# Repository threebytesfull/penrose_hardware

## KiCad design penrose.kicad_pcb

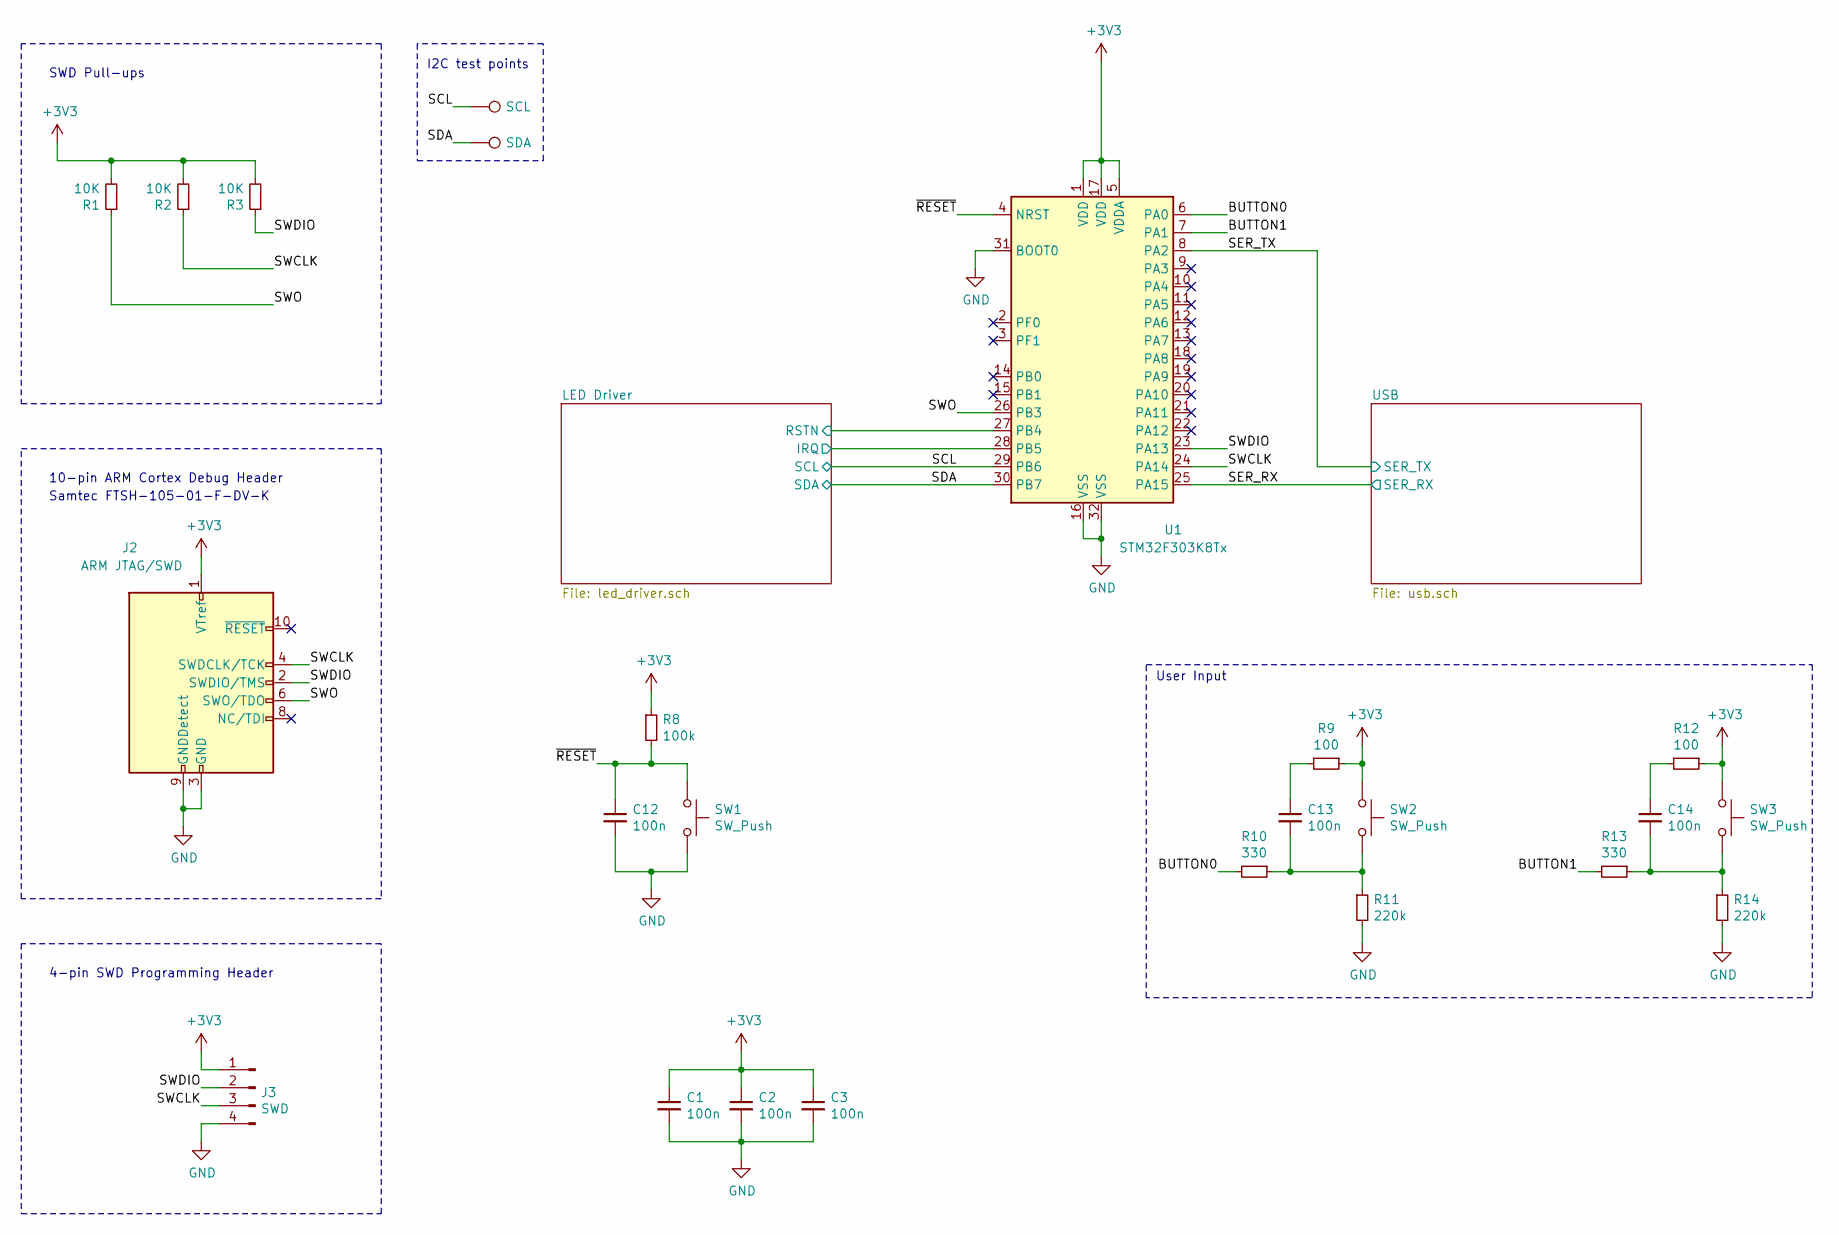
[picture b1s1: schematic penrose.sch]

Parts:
C1, C2, C3, C12, C13, C14: 100n; C_0603_1608Metric
J2: ARM JTAG/SWD; FTSH-105-01-F-DV-K_HandSolder
J3: SWD; Harwin_M20-88900445_1x04_P2.54mm_Horizontal
R1, R2, R3: 10K; R_0603_1608Metric
R8: 100k; R_0603_1608Metric
R9, R12: 100; R_0603_1608Metric
R10, R13: 330; R_0603_1608Metric
R11, R14: 220k; R_0603_1608Metric
SW1, SW2, SW3: SW_Push; SW_SPST_B3U-1000P_HandSolder
TP12: SCL; TestPoint_Pad_D1.0mm
TP13: SDA; TestPoint_Pad_D1.0mm
U1: STM32F303K8Tx; LQFP-32_7x7mm_P0.8mm_Clear

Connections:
+3V3: C1.1, C2.1, C3.1, J2.1 (VTref), J3.1, R1.2, R2.2, R3.2, R8.1, R9.1, R12.1, SW2.1, SW3.1, U1.1 (VDD), U1.5 (VDDA), U1.17 (VDD); also elsewhere on the board
/BUTTON0: R10.2, U1.6 (PA0)
/BUTTON1: R13.2, U1.7 (PA1)
/LED Driver/IRQ: U1.28 (PB5); also elsewhere on the board
/LED Driver/RSTN: U1.27 (PB4); also elsewhere on the board
/SCL: TP12.1, U1.29 (PB6); also elsewhere on the board
/SDA: TP13.1, U1.30 (PB7); also elsewhere on the board
/SER_RX: U1.25 (PA15); also elsewhere on the board
/SER_TX: U1.8 (PA2); also elsewhere on the board
/SWCLK: J2.4 (SWDCLK/TCK), J3.3, R2.1, U1.24 (PA14)
/SWDIO: J2.2 (SWDIO/TMS), J3.2, R3.1, U1.23 (PA13)
/SWO: J2.6 (SWO/TDO), R1.1, U1.26 (PB3)
/~RESET: C12.1, R8.2, SW1.1, U1.4 (NRST)
GND: C1.2, C2.2, C3.2, C12.2, J2.3 (GND), J2.5 (GND), J2.9 (GNDDetect), J3.4, R11.2, R14.2, SW1.2, U1.16 (VSS), U1.31 (BOOT0), U1.32 (VSS); also elsewhere on the board
unnamed: C13.1, R9.2
unnamed: C13.2, R10.1, R11.1, SW2.2
unnamed: C14.1, R12.2
unnamed: C14.2, R13.1, R14.1, SW3.2

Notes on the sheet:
4-pin SWD Programming Header
10-pin ARM Cortex Debug Header
SWD Pull-ups
Samtec FTSH-105-01-F-DV-K
I2C test points
User Input

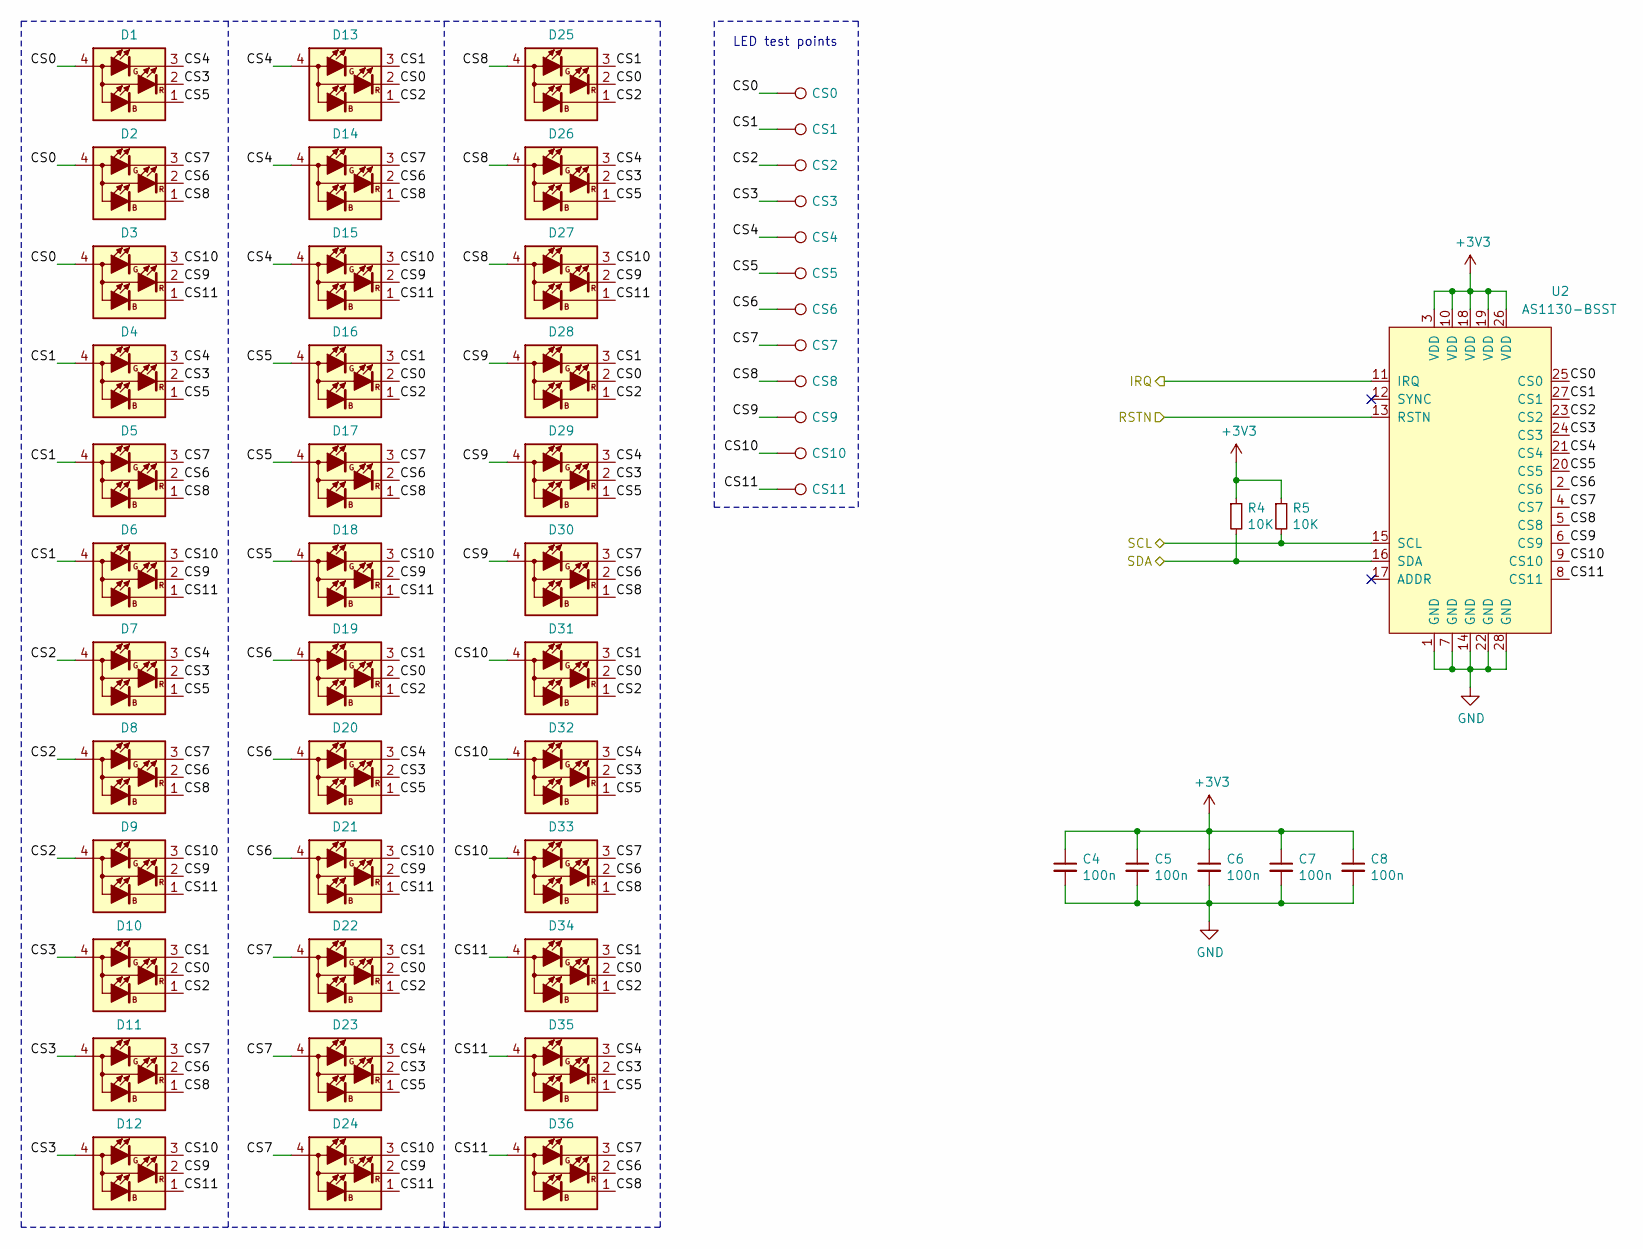
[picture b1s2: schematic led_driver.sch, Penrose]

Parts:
C4, C5, C6, C7, C8: 100n; C_0603_1608Metric
D1, D2, D3, D4, D5, D6, D7, D8, D9, D10, D11, D12, D13, D14, D15, D16, D17, D18, D19, D20, D21, D22, D23, D24, D25, D26, D27, D28, D29, D30, D31, D32, D33, D34, D35, D36: ARGB1313HS-TR_CommonAnode; LED_0808_Metric2020_CommonAnode
R4, R5: 10K; R_0603_1608Metric
TP0: CS0; TestPoint_Pad_D1.0mm
TP1: CS1; TestPoint_Pad_D1.0mm
TP2: CS2; TestPoint_Pad_D1.0mm
TP3: CS3; TestPoint_Pad_D1.0mm
TP4: CS4; TestPoint_Pad_D1.0mm
TP5: CS5; TestPoint_Pad_D1.0mm
TP6: CS6; TestPoint_Pad_D1.0mm
TP7: CS7; TestPoint_Pad_D1.0mm
TP8: CS8; TestPoint_Pad_D1.0mm
TP9: CS9; TestPoint_Pad_D1.0mm
TP10: CS10; TestPoint_Pad_D1.0mm
TP11: CS11; TestPoint_Pad_D1.0mm
U2: AS1130-BSST; SSOP-28_5.3x10.2mm_P0.65mm_Clear

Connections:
+3V3: C4.1, C5.1, C6.1, C7.1, C8.1, R4.1, R5.1, U2.3 (VDD), U2.10 (VDD), U2.18 (VDD), U2.19 (VDD), U2.26 (VDD); also elsewhere on the board
/LED Driver/CS0: D1.4 (A), D2.4 (A), D3.4 (A), D10.2 (KR), D13.2 (KR), D16.2 (KR), D19.2 (KR), D22.2 (KR), D25.2 (KR), D28.2 (KR), D31.2 (KR), D34.2 (KR), TP0.1, U2.25 (CS0)
/LED Driver/CS1: D4.4 (A), D5.4 (A), D6.4 (A), D10.3 (KG), D13.3 (KG), D16.3 (KG), D19.3 (KG), D22.3 (KG), D25.3 (KG), D28.3 (KG), D31.3 (KG), D34.3 (KG), TP1.1, U2.27 (CS1)
/LED Driver/CS2: D7.4 (A), D8.4 (A), D9.4 (A), D10.1 (KB), D13.1 (KB), D16.1 (KB), D19.1 (KB), D22.1 (KB), D25.1 (KB), D28.1 (KB), D31.1 (KB), D34.1 (KB), TP2.1, U2.23 (CS2)
/LED Driver/CS3: D1.2 (KR), D4.2 (KR), D7.2 (KR), D10.4 (A), D11.4 (A), D12.4 (A), D20.2 (KR), D23.2 (KR), D26.2 (KR), D29.2 (KR), D32.2 (KR), D35.2 (KR), TP3.1, U2.24 (CS3)
/LED Driver/CS4: D1.3 (KG), D4.3 (KG), D7.3 (KG), D13.4 (A), D14.4 (A), D15.4 (A), D20.3 (KG), D23.3 (KG), D26.3 (KG), D29.3 (KG), D32.3 (KG), D35.3 (KG), TP4.1, U2.21 (CS4)
/LED Driver/CS5: D1.1 (KB), D4.1 (KB), D7.1 (KB), D16.4 (A), D17.4 (A), D18.4 (A), D20.1 (KB), D23.1 (KB), D26.1 (KB), D29.1 (KB), D32.1 (KB), D35.1 (KB), TP5.1, U2.20 (CS5)
/LED Driver/CS6: D2.2 (KR), D5.2 (KR), D8.2 (KR), D11.2 (KR), D14.2 (KR), D17.2 (KR), D19.4 (A), D20.4 (A), D21.4 (A), D30.2 (KR), D33.2 (KR), D36.2 (KR), TP6.1, U2.2 (CS6)
/LED Driver/CS7: D2.3 (KG), D5.3 (KG), D8.3 (KG), D11.3 (KG), D14.3 (KG), D17.3 (KG), D22.4 (A), D23.4 (A), D24.4 (A), D30.3 (KG), D33.3 (KG), D36.3 (KG), TP7.1, U2.4 (CS7)
/LED Driver/CS8: D2.1 (KB), D5.1 (KB), D8.1 (KB), D11.1 (KB), D14.1 (KB), D17.1 (KB), D25.4 (A), D26.4 (A), D27.4 (A), D30.1 (KB), D33.1 (KB), D36.1 (KB), TP8.1, U2.5 (CS8)
/LED Driver/CS9: D3.2 (KR), D6.2 (KR), D9.2 (KR), D12.2 (KR), D15.2 (KR), D18.2 (KR), D21.2 (KR), D24.2 (KR), D27.2 (KR), D28.4 (A), D29.4 (A), D30.4 (A), TP9.1, U2.6 (CS9)
/LED Driver/CS10: D3.3 (KG), D6.3 (KG), D9.3 (KG), D12.3 (KG), D15.3 (KG), D18.3 (KG), D21.3 (KG), D24.3 (KG), D27.3 (KG), D31.4 (A), D32.4 (A), D33.4 (A), TP10.1, U2.9 (CS10)
/LED Driver/CS11: D3.1 (KB), D6.1 (KB), D9.1 (KB), D12.1 (KB), D15.1 (KB), D18.1 (KB), D21.1 (KB), D24.1 (KB), D27.1 (KB), D34.4 (A), D35.4 (A), D36.4 (A), TP11.1, U2.8 (CS11)
/LED Driver/IRQ: U2.11 (IRQ); also elsewhere on the board
/LED Driver/RSTN: U2.13 (RSTN); also elsewhere on the board
/SCL: R5.2, U2.15 (SCL); also elsewhere on the board
/SDA: R4.2, U2.16 (SDA); also elsewhere on the board
GND: C4.2, C5.2, C6.2, C7.2, C8.2, U2.1 (GND), U2.7 (GND), U2.14 (GND), U2.22 (GND), U2.28 (GND); also elsewhere on the board

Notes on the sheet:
LED test points

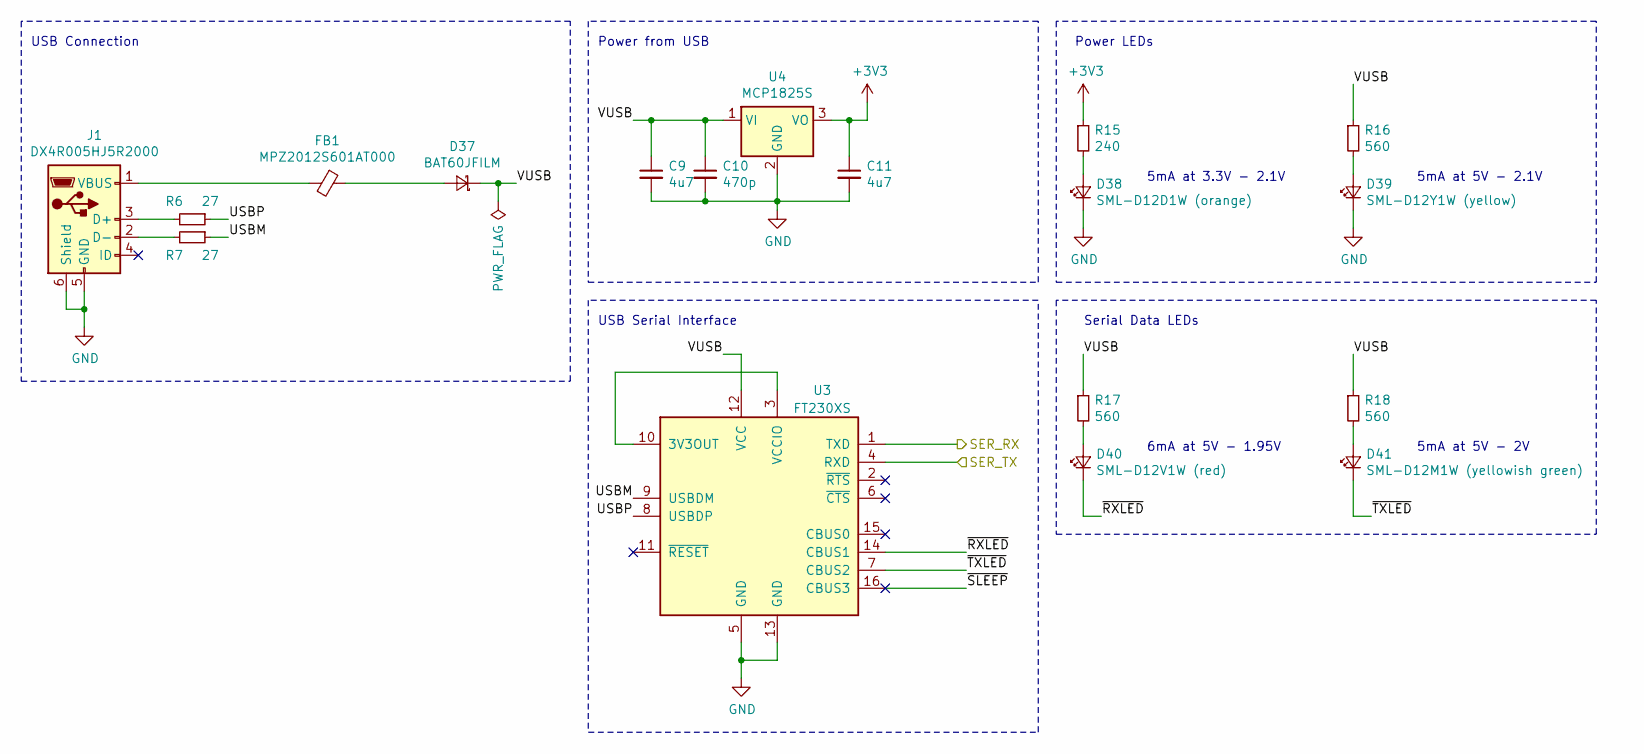
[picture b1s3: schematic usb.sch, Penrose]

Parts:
C9, C11: 4u7; C_0603_1608Metric
C10: 470p; C_0603_1608Metric
D37: BAT60JFILM; D_SOD-323_HandSoldering
D38: SML-D12D1W (orange); LED_0603_1608Metric
D39: SML-D12Y1W (yellow); LED_0603_1608Metric
D40: SML-D12V1W (red); LED_0603_1608Metric
D41: SML-D12M1W (yellowish green); LED_0603_1608Metric
FB1: MPZ2012S601AT000; L_0805_2012Metric
J1: DX4R005HJ5R2000; DX4R005HJ5_HandSolder
R6, R7: 27; R_0603_1608Metric
R15: 240; R_0603_1608Metric
R16, R17, R18: 560; R_0603_1608Metric
U3: FT230XS; SSOP-16_3.9x4.9mm_P0.635mm_Clear
U4: MCP1825S; SOT-223-3_TabPin2

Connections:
+3V3: C11.1, R15.1, U4.3 (VO); also elsewhere on the board
/SER_RX: U3.1 (TXD); also elsewhere on the board
/SER_TX: U3.4 (RXD); also elsewhere on the board
/USB/USBM: R7.1, U3.9 (USBDM)
/USB/USBP: R6.1, U3.8 (USBDP)
/USB/VUSB: C9.1, C10.1, D37.1 (K), R16.1, R17.1, R18.1, U3.12 (VCC), U4.1 (VI)
/USB/~RXLED: D40.1 (K), U3.14 (CBUS1)
/USB/~TXLED: D41.1 (K), U3.7 (CBUS2)
GND: C9.2, C10.2, C11.2, D38.1 (K), D39.1 (K), J1.5 (GND), J1.6 (Shield), U3.5 (GND), U3.13 (GND), U4.2 (GND); also elsewhere on the board
unnamed: D37.2 (A), FB1.1
unnamed: D38.2 (A), R15.2
unnamed: D39.2 (A), R16.2
unnamed: D40.2 (A), R17.2
unnamed: D41.2 (A), R18.2
unnamed: FB1.2, J1.1 (VBUS)
unnamed: J1.2 (D-), R7.2
unnamed: J1.3 (D+), R6.2
unnamed: U3.3 (VCCIO), U3.10 (3V3OUT)

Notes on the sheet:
5mA at 5V - 2.1V
5mA at 3.3V - 2.1V
5mA at 5V - 2V
6mA at 5V - 1.95V
Power LEDs
Serial Data LEDs
Power from USB
USB Serial Interface
USB Connection

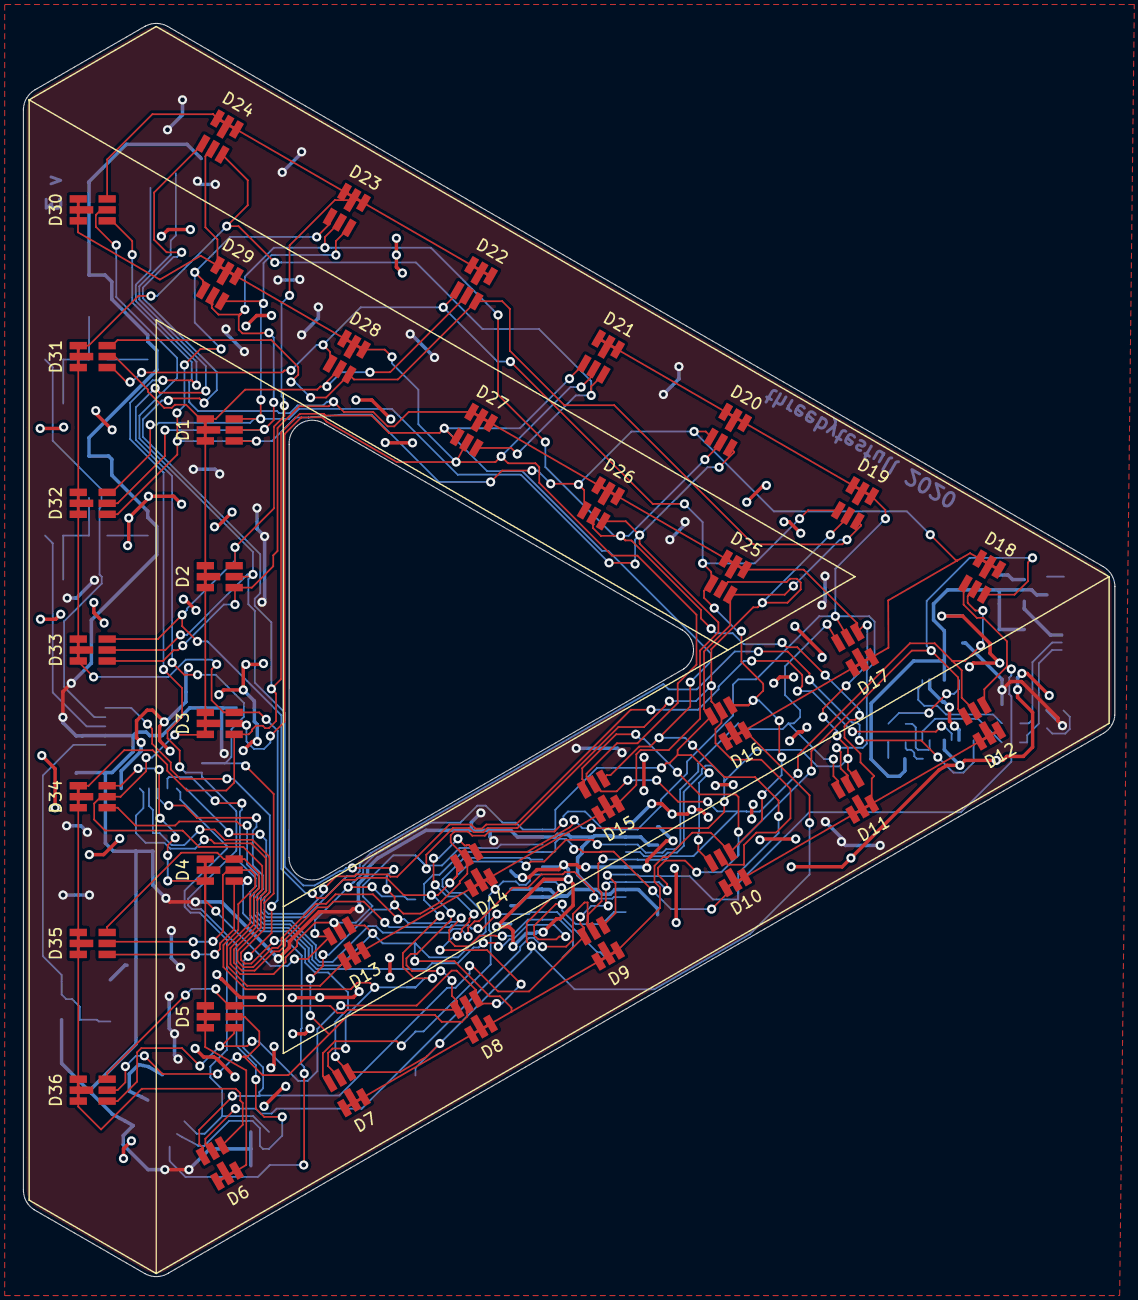
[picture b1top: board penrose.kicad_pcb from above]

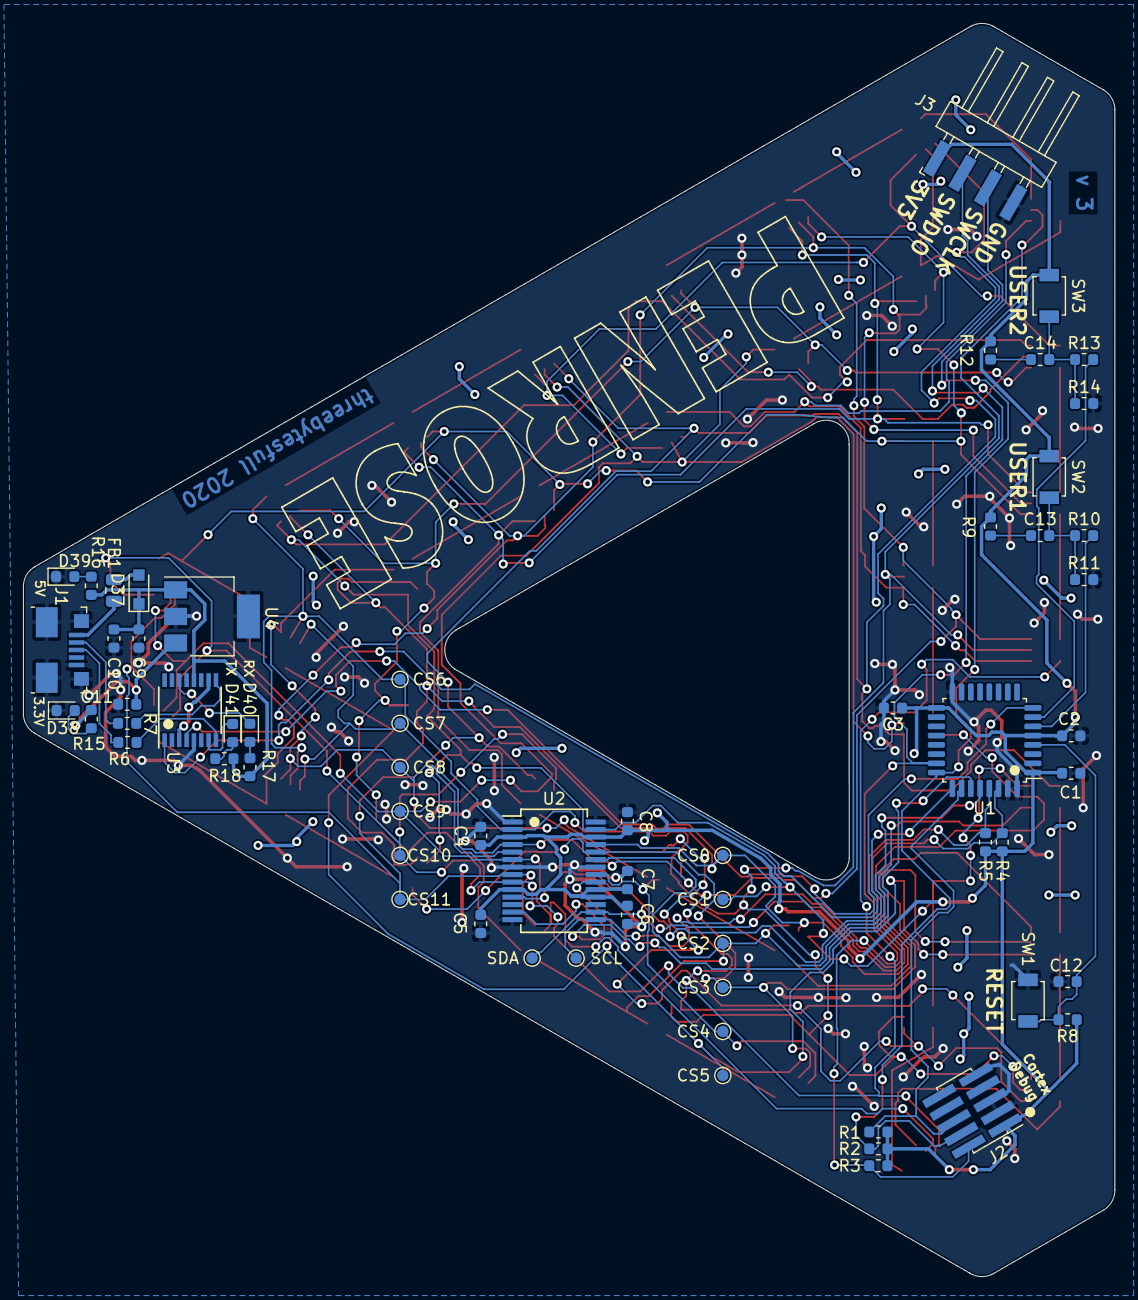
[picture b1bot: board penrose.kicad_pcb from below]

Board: 2 copper layers, 94.5 x 108.5 mm, 98 parts (62 on the bottom side), 44 nets.

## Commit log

2020-04-11 Add Penrose v3 project files
